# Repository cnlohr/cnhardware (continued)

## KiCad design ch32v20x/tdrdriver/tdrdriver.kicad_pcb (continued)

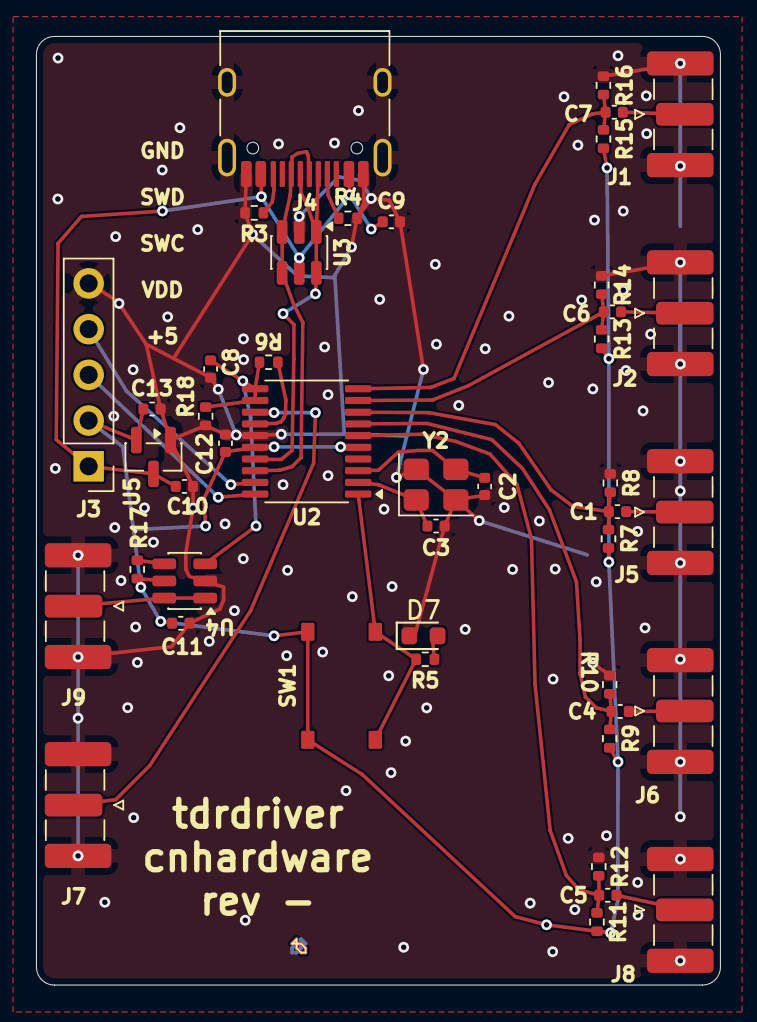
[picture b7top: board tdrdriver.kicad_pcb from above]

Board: 2 copper layers, 38.0 x 52.7 mm, 45 parts (0 on the bottom side), 28 nets.

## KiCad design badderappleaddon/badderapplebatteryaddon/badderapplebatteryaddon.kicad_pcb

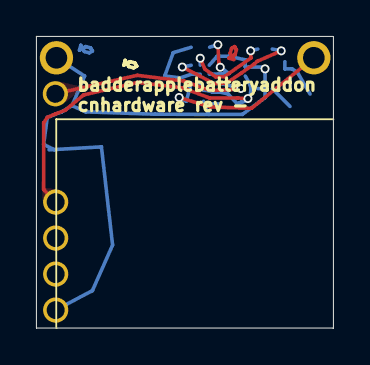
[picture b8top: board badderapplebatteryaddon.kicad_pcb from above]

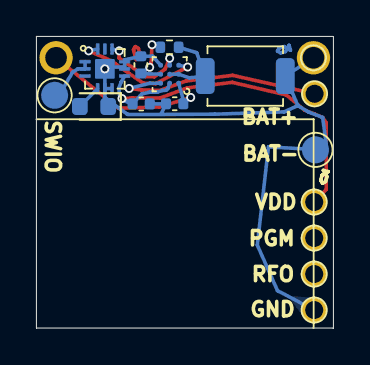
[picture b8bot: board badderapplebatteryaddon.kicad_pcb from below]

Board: 2 copper layers, 16.5 x 16.2 mm, 17 parts (16 on the bottom side), 10 nets.

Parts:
C1, C2: 100n; C_0402_1005Metric
C3: 1u; C_0402_1005Metric
D1: LED; LED_0603_1608Metric
J3: PGM; TestPoint_Pad_D1.0mm
J4: VDD; TestPoint_Pad_D1.0mm
J5, J11: GND; TestPoint_Pad_D1.0mm
J6: RFO; TestPoint_Pad_D1.0mm
J7: BAT+; TestPoint_Pad_D1.0mm
J10: VBUS
J82: SWIO; TestPoint_Pad_D1.5mm
R6: 5.1k; R_0402_1005Metric
SW1: TS; SW_SPST_TS-1088-xR020
TP13: BAT-; TestPoint_Pad_D1.5mm
U1: WLCSP-9-P0.5mm
U2: CH32V005D6U6; QFN-12-P0.4-WCH

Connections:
GND: C1.2, C2.2, C3.2, D1.1 (K), J5.1 (1_1), J11.1 (1_1), SW1.3 (B), TP13.1 (1_1), U1.C3 (GND), U2.2 (PA2/T1C2N/OPP0/XO/A0), U2.3 (PD0/T1C1N/SDA_/TX_/OPN1), U2.5 (PC0/T1C3_/T2C3), U2.6 (PC3/T1C3/T1C1N_), U2.13 (PAD)
LED: D1.2 (A), U2.1 (PA1/T1C2/OPN0/XI/A1)
unnamed: J82.1 (1_1), U2.10 (PD1/SWIO/T1C3N/SCL_/RX_), U2.11 (PD4/T1C4_/T2C1/OPO/A7)
PWRINT: R6.1, SW1.1 (A), U1.B1 (NTC), U1.B2 (INT)
SCL: U1.C2 (SCL), U2.7 (PC4/T1C4/T1C1_/T1C2N/MCO/A2)
SDA: U1.C1 (SDA), U2.9 (PC7/T1C2_/T2C2_)
VBAT: J7.1 (1_1), U1.A3 (BAT)
VBUS: C2.1, J10.1 (1_1), U1.A1 (IN)
VDD: C1.1, J4.1 (1_1), U1.A2 (SYS), U2.4 (VDD)
VSYS: C3.1, R6.2, U1.B3 (VDD)

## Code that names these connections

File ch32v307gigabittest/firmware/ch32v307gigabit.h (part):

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#endif

#ifndef CH32V307GIGABIT_PHY_RSTB
#define CH32V307GIGABIT_PHY_RSTB PA10
#endif


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	funDigitalWrite( CH32V307GIGABIT_PHY_RSTB, FUN_LOW );

	// Configure strapping.
	funPinMode( PA1, GPIO_CFGLR_IN_PUPD ); // GMII_RXD3
	funPinMode( PA0, GPIO_CFGLR_IN_PUPD ); // GMII_RXD2
	funPinMode( PC3, GPIO_CFGLR_IN_PUPD ); // GMII_RXD1
	funPinMode( PC2, GPIO_CFGLR_IN_PUPD ); // GMII_RXD0
	funDigitalWrite( PA1, FUN_HIGH );
	funDigitalWrite( PA0, FUN_HIGH );
	funDigitalWrite( PC3, FUN_HIGH ); // No TX Delay
	funDigitalWrite( PC2, FUN_HIGH );

	// Pull-up MDIO
	funPinMode( PD9, GPIO_CFGLR_OUT_50Mhz_PP ); //Pull-up control (DO NOT CHECK IN, ADD RESISTOR)
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
	// Switch to PLL.
#ifdef CH32V307GIGABIT_MCO25
	RCC->CFGR0 = (RCC->CFGR0 & ~RCC_SW) | RCC_SW_PLL | (9<<24); // And output clock on PA8
#else
	RCC->CFGR0 = (RCC->CFGR0 & ~RCC_SW) | RCC_SW_PLL;
#endif

	// For clock in.
	funPinMode( PB1, GPIO_CFGLR_IN_FLOAT ); //GMII_CLK125

	RCC->CFGR2 |= RCC_ETH1G_125M_EN; // Enable 125MHz clock.

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	// Use RGMII
	EXTEN->EXTEN_CTR |= EXTEN_ETH_RGMII_SEL; //EXTEN_ETH_RGMII_SEL;

	funPinMode( PB13, GPIO_CFGLR_OUT_50Mhz_AF_PP ); //GMII_MDIO
	funPinMode( PB12, GPIO_CFGLR_OUT_50Mhz_AF_PP ); //GMII_MDC

	// For clock output to Ethernet module.
	funPinMode( PA8, GPIO_CFGLR_OUT_50Mhz_AF_PP ); // PHY_CKTAL

	// Release PHY from reset.
	funDigitalWrite( CH32V307GIGABIT_PHY_RSTB, FUN_HIGH );

	funPinMode( PB0, GPIO_CFGLR_OUT_50Mhz_AF_PP ); // GMII_TXD3
	funPinMode( PC5, GPIO_CFGLR_OUT_50Mhz_AF_PP ); // GMII_TXD2
	funPinMode( PC4, GPIO_CFGLR_OUT_50Mhz_AF_PP ); // GMII_TXD1
	funPinMode( PA7, GPIO_CFGLR_OUT_50Mhz_AF_PP ); // GMII_TXD0
	funPinMode( PA3, GPIO_CFGLR_OUT_50Mhz_AF_PP ); // GMII_TXCTL
	funPinMode( PA2, GPIO_CFGLR_OUT_50Mhz_AF_PP ); // GMII_TXC
	funPinMode( PA1, GPIO_CFGLR_IN_PUPD ); // GMII_RXD3
	funPinMode( PA0, GPIO_CFGLR_IN_PUPD ); // GMII_RXD2
	funPinMode( PC3, GPIO_CFGLR_IN_PUPD ); // GMII_RXD1
	funPinMode( PC2, GPIO_CFGLR_IN_PUPD ); // GMII_RXD0
	funPinMode( PC1, GPIO_CFGLR_IN_PUPD ); // GMII_RXCTL
	funPinMode( PC0, GPIO_CFGLR_IN_FLOAT ); // GMII_RXC

	funDigitalWrite( PA1, FUN_HIGH ); // SELGRV = 3.3V
	funDigitalWrite( PA0, FUN_HIGH ); // TXDelay = 1
	funDigitalWrite( PC3, FUN_HIGH ); // AN[0] = 1
	funDigitalWrite( PC2, FUN_HIGH ); // AN[1] = 1
	funDigitalWrite( PC1, FUN_LOW );  // PHYAD[0]

	// Power on and reset.
	RCC->AHBPCENR |= RCC_ETHMACEN | RCC_ETHMACTXEN | RCC_ETHMACRXEN;
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
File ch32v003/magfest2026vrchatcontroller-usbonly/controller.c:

#include "ch32fun.h"
#include <stdio.h>
#include <string.h>
#include "rv003usb.h"

uint32_t clickcount = 0;
uint32_t clickcount_raw = 0;
uint32_t activate_time = 0;
int is_activated = 0;

//6 seconds
#define BONUS_TIME 240000000
#define MAX_CLICKS 420

typedef struct {
	volatile uint8_t len;
	uint8_t buffer[8];
} midi_message_t;

midi_message_t midi_in;

// midi data from device -> host (IN)
void midi_send(uint8_t * msg, uint8_t len)
{
	memcpy( midi_in.buffer, msg, len );
	midi_in.len = len;
}
#define midi_send_ready() (midi_in.len == 0)

// Set up PC2 to PC5 as inputs
void keyboard_init( void )
{
	// Enable GPIOC
	RCC->APB2PCENR |= RCC_APB2Periph_GPIOC | RCC_APB2Periph_GPIOD | RCC_APB2Periph_GPIOA | RCC->APB2PCENR | RCC_APB2Periph_USART1 | RCC_APB2Periph_AFIO;

	funDigitalWrite( PA1, 1 );
	funDigitalWrite( PA2, 1 );
	funDigitalWrite( PD2, 1 );
	funDigitalWrite( PD6, 1 );
	funDigitalWrite( PD7, 1 );
	funDigitalWrite( PC0, 1 );
	funDigitalWrite( PC1, 1 );
	funDigitalWrite( PC2, 1 );
	funDigitalWrite( PC3, 1 );
	funDigitalWrite( PC4, 1 );
	funDigitalWrite( PC5, 1 );
	funDigitalWrite( PC6, 1 );
	funDigitalWrite( PC7, 1 );

	funPinMode( PA1, GPIO_CFGLR_IN_PUPD );
	funPinMode( PA2, GPIO_CFGLR_IN_PUPD );
	funPinMode( PD2, GPIO_CFGLR_IN_PUPD );
	funPinMode( PD6, GPIO_CFGLR_IN_PUPD );
	funPinMode( PD7, GPIO_CFGLR_IN_PUPD );
	funPinMode( PC0, GPIO_CFGLR_IN_PUPD );
	funPinMode( PC1, GPIO_CFGLR_IN_PUPD );
	funPinMode( PC2, GPIO_CFGLR_IN_PUPD );
	funPinMode( PC3, GPIO_CFGLR_IN_PUPD );
	funPinMode( PC4, GPIO_CFGLR_IN_PUPD );
	funPinMode( PC5, GPIO_CFGLR_IN_PUPD );
	funPinMode( PC6, GPIO_CFGLR_IN_PUPD );
	funPinMode( PC7, GPIO_CFGLR_IN_PUPD );


	// Set UART baud rate here
	#define UART_BR 115200

	// Push-Pull, 10MHz Output on D0, with AutoFunction, USART1_RM=01
	funPinMode( PD0, GPIO_CFGLR_OUT_10Mhz_AF_PP );

	AFIO->PCFR1 = AFIO_PCFR1_USART1_REMAP;

	// Setup UART for Tx 8n1
	USART1->CTLR1 = USART_WordLength_8b | USART_Parity_No | USART_Mode_Tx;
	USART1->CTLR2 = USART_StopBits_2;

	// Set baud rate and enable UART
	USART1->BRR = ((FUNCONF_SYSTEM_CORE_CLOCK) + (UART_BR)/2) / (UART_BR);
	USART1->CTLR1 |= CTLR1_UE_Set;
}

void scan_keyboard(void)
{
	uint32_t input = GPIOC->INDR | ( GPIOD->INDR << 8 ) | ( GPIOA->INDR<<16);
	static uint32_t last_input;
	static uint32_t last_down[24];
	input &= 0b1101100010011111111;
	
	int dcc = 0;
	int i;
	uint32_t mask = input ^ last_input;
	mask &= ~input;
	uint32_t now = SysTick->CNT;
	static uint32_t pending = 0;

	// Debounce down press only.
	for( i = 0; i < 24; i++ )
	{
		if( (mask & (1<<i)) )
		{
			last_down[i] = now;
			pending |= (1<<i);
		}
		if( (now - last_down[i]) > 960000 ) //20ms debounce
		{
			if( (pending&(1<<i)) )
			{
				if( ( input & (1<<i)) == 0 ) 
					dcc++;
			}
			pending&=~(1<<i);
		}

	}
	clickcount+=dcc;
	clickcount_raw+=dcc;

	if( clickcount >= MAX_CLICKS && !is_activated )
	{
		clickcount = MAX_CLICKS;
		is_activated = 1;
		activate_time = SysTick->CNT;
	}

	if( is_activated && ( (SysTick->CNT - activate_time) > BONUS_TIME ) )
	{
		is_activated = 0;
		activate_time = 0;
		clickcount = 0;
	}

	if( midi_send_ready() )
	{
		uint8_t midi_msg[4] = {0x09, 0xB0, 0x40, 0x7F}; // Control Channel
		midi_msg[2] = (clickcount >> 3);
		midi_msg[3] = (clickcount & 7)<<4;
//printf( "%d\n", clickcount );
		midi_send(midi_msg, 4);
	}

	last_input = input;
}

int main()
{
	SystemInit();
	keyboard_init();
	usb_setup();
	int fct = 0;
	while(1)
	{
		scan_keyboard();

		if((fct & 0x7)== 0)
		{
			USART1->DATAR = (clickcount_raw & 0x3f) | ( is_activated ? 0x80 : 0x00);
			//printf( "!\n" );
		}
		Delay_Us(200);
		fct++;
	}
}

void usb_handle_user_in_request( struct usb_endpoint * e, uint8_t * scratchpad, int endp, uint32_t sendtok, struct rv003usb_internal * ist )
{
	if (endp && midi_in.len) {
		usb_send_data( midi_in.buffer, midi_in.len, 0, sendtok );
		midi_in.len = 0;
	} else {
		usb_send_empty( sendtok );
	}
}

void usb_handle_other_control_message( struct usb_endpoint * e, struct usb_urb * s, struct rv003usb_internal * ist )
{
	LogUEvent( SysTick->CNT, s->wRequestTypeLSBRequestMSB, s->lValueLSBIndexMSB, s->wLength );
}

void usb_handle_user_data( struct usb_endpoint * e, int current_endpoint, uint8_t * data, int len, struct rv003usb_internal * ist )
{
//	if (len); //midi_receive(data);
//	if (len==8); //midi_receive(&data[4]);
}






/*

using UdonSharp;
using UnityEngine;
using VRC.SDKBase;
using VRC.Udon;

using TMPro;
public class MidiReceiver : UdonSharpBehaviour
{
	public TMP_Text tmp;
	public int frameno;
	
	public int lastVelocity;
	public int lastNoteNo;
	public int lastPercent420;
	
    void Start()
    {
        Debug.Log( "test" );
    }
	
	override public void MidiControlChange(int channel, int number, int velocity)
	{
		Debug.Log( $"MidiControlChange {channel} {number} {velocity}" );
		lastVelocity = velocity;
		lastNoteNo = number;
		lastPercent420 = number * 8 + velocity/16;
	}
	
	override public void MidiNoteOn(int channel, int number, int velocity)
	{
		Debug.Log( $"MidiNoteOn {channel} {number} {velocity}" );
		lastVelocity = velocity;
		lastNoteNo = number;
		lastPercent420 = number * 8 + velocity/16;
	}
	
	
	void Update()
	{
		frameno++;
		tmp.text = $"N:{frameno}\n{lastPercent420}";
	}
}
*/

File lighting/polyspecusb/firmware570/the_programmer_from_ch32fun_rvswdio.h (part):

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
#define CH5xx_SUPPORT 1

//#define POWER_IO    PA7
//#define SWC_IO      PA3
//#define SWD_IO      PA2

#define BB_PRINTF_DEBUG(x...) // printf( x )
#define IRAM_ATTR __HIGH_CODE
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						iptr += 6; // reserved + SDM values.
						(void)use_apll;
						(void)sdm0;
						// Output MCO clock on PC4.
						// Not implemented on 570
					}
					break;
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
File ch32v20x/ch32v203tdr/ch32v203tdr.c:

/* Small example showing how to use the SWIO programming pin to 
   do printf through the debug interface */

#include "ch32fun.h"
#include <stdio.h>

uint32_t count;

int main()
{
	SystemInit();

	// Force HSE.
	

	RCC->APB2PCENR |= RCC_APB2Periph_GPIOD | RCC_APB2Periph_GPIOC | RCC_APB2Periph_GPIOA | RCC_APB2Periph_TIM1 | RCC_APB2Periph_ADC1;

	RCC->CFGR0 |= RCC_ADCPRE_DIV8; // Divide ADC timer
	RCC->CTLR &= ~3; // HSI Off

	// Configure ADC first.
	// Note to self: DO NOT USE BUFFER
	ADC1->CTLR1 = ( 0 << 0);
	ADC1->CTLR2 = ADC_EXTTRIG | ADC_ADON | ( 0 << 17 ); // EXTSEL = T1CC1
	ADC1->SAMPTR2 = 0; // 1.5 cycle SAMPTR = 0, 1 = 7.5 samples, does not change edge

	// Prescaler (Actually run TIM1 @ 144MHz)
	TIM1->PSC = 0x0000;


	// Actual time is this+1
	// Must be divisible by ADC setup.
	TIM1->ATRLR = 511;

	TIM1->SWEVGR |= TIM_UG;
	
	TIM1->CCER |= TIM_CC1E | TIM_CC1P;
	TIM1->CCER |= TIM_CC4E | TIM_CC4P;
	TIM1->CHCTLR1 |= TIM_OC1M_2 | TIM_OC1M_1;
	TIM1->CHCTLR2 |= TIM_OC4M_2 | TIM_OC4M_1;

	TIM1->CH1CVR = 68; // CH1 triggers ADC.  Be careful where this is set.
	TIM1->CH4CVR = 4; // This is what we are controlling.

	TIM1->CTLR1 = 0;

	// Enable TIM1 outputs
	TIM1->BDTR |= TIM_MOE;
	TIM1->CTLR1 |= TIM_CEN;

	funPinMode( PA0, GPIO_CNF_IN_ANALOG );

	// PWM outputs.  We only actually use PA11, PA8 is diagnostic for the ADC trigger.
	funPinMode( PA8, GPIO_Speed_50MHz | GPIO_CNF_OUT_PP_AF );
	funPinMode( PA9, GPIO_Speed_50MHz | GPIO_CNF_OUT_PP_AF );
	funPinMode( PA10, GPIO_Speed_50MHz | GPIO_CNF_OUT_PP_AF );
	funPinMode( PA11, GPIO_Speed_50MHz | GPIO_CNF_OUT_PP_AF );

	int framestart = 60;
	int frame = framestart;
	int32_t vals[128];

	while(1)
	{
		memset( vals, 0, sizeof( vals ) );
		int i;
		(void)ADC1->RDATAR;
		for( i = 30; i < 92; i++ )
		{
			int j;
			for( j = 0; j < 16; j++ )
			{
				while(!(ADC1->STATR & ADC_EOC));
				vals[i] += ADC1->RDATAR;
				TIM1->CH4CVR = i;
			}
		}
		for( i = 30; i < 92; i++ )
		{
			printf( "%d ", (int)vals[i] );
		}
		printf( "\n" );
	}
}

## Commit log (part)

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2025-06-28 Tweak parts
2025-07-08 Undo Update README.md
2025-07-08 Add stuff for inductance tracking
2025-07-09 Update some new parts
2025-07-09 Add datasheet
2025-07-11 Add some missing hardware
2025-07-12 Add ch570 saob test
2025-07-12 Update PCB
2025-07-12 Bump design
2025-07-12 Add keytar touch
2025-07-12 Update kboards for ordering
2025-07-12 Update with kicad stuff
2025-07-12 Update design
2025-07-13 Bump versions
2025-07-13 Bump
2025-07-18 Bump keytar files
2025-07-19 Bump itty bitty
2025-07-19 Bump kicad parts
2025-07-20 Bump ittyahrs
2025-07-20 Tweak tinyahrs
2025-07-20 Tweaking board
2025-07-21 Bump hexi test
2025-07-22 Playing with other structures
2025-07-22 Poking around
2025-07-26 Add test firmware
2025-07-26 Update with notes to do.
2025-07-26 Basic firmware test
2025-07-26 Add ch570 port of the sao game.
2025-07-26 Bump sao game
2025-07-26 Update firmwares
2025-07-27 bump config
2025-07-27 Bump designs
2025-07-27 Add some basic test stuff. No QMI yet.
2025-07-28 Working firmware examples
2025-07-28 Bump design overall
2025-07-28 Add some neat adc stuff
2025-07-28 Bump code test
2025-07-29 Bump ch570 design
2025-07-30 Bump technique using sleep
2025-07-30 Add timer based mechanism for ADC
2025-07-30 bump exploration
2025-07-30 make main loop control release, etc.
2025-07-30 Add buck
2025-08-05 Update design with new ch570 board
2025-08-05 Update designs
2025-08-05 Poke design
2025-08-05 Bump submodule
2025-08-06 Bump all designs per order
2025-08-07 Working on design
2025-08-08 Bump design by order
2025-08-08 Bump all designs for order
2025-08-08 Bump designs per purchase
2025-08-08 Bump based on actual board order
2025-08-17 resaved scheamtci
2025-08-19 Add notes about repo moving
2025-08-22 Add some parts
2025-08-22 Bump aa only swadge
2025-08-22 Tweak design
2025-08-24 Bump library
2025-08-24 Bump aa swadge
2025-08-24 Bump with new wsled changes
2025-08-24 Update with revA for 006 board
2025-08-29 Bump with thinking about ch570 swadge
2025-08-31 List some up/down converters
2025-09-01 Bump readme
2025-09-03 Update with addlepated array
2025-09-04 Update parts
2025-09-07 Bump disign!
2025-09-08 Bump amp
2025-09-08 Update notes on amp
2025-09-10 Tweak designs
2025-09-10 Forgot to commit component
2025-09-28 Bump gigabit test
2025-09-30 update rev as it's in the other repo but leave it here
2025-10-03 Cleanup making the usb connector have paste
2025-10-03 Thicken power traces, use a SOT-23 regulator
2025-10-28 9v battery sao test
2025-10-29 Bump with battery model
2025-11-04 Bump scope
2025-11-05 Update scope
2025-11-05 revert upping design
2025-11-10 Bump 9v sao
2025-11-10 Fix based on comments from fab
2025-11-10 add ch32v208 part
2025-11-10 Update to actual pritn
2025-11-16 fix version
2025-11-16 Udpate design
2025-11-16 Update with opa564
2025-11-18 Revert version
2025-11-18 Add notes in todo
2025-11-18 Update with basic idea
2025-11-19 Bump lib
2025-11-20 Bump design per order
2025-11-25 Working firmware in i2c and spi
2025-11-25 Add basic test example with adc
2025-11-25 Change name
2025-11-25 ADd notes
2025-11-25 Update with timing note
2025-11-25 cleanup
2025-11-25 Update notes
2025-11-26 Update tiatest with functional rev
2025-11-26 Update part
2025-11-26 Add testing code
2025-11-27 Working with vsync ~170Hz
2025-11-30 Add a sleep mode
2025-11-30 Add some code for a raw smps test
2025-12-01 examining a pfs programmer
2025-12-03 Update with notes about charge pumps
2025-12-03 Per order
2025-12-05 Update with a basic emulator
2025-12-05 update emu getting closer
2025-12-06 Update firmware to allow for emulated pressure
2025-12-08 Fixup firmware for using full dual sets.
2025-12-08 Fixup timings for 3 strips simultaneously
2025-12-08 Move project
2025-12-08 Add move note
2025-12-11 Update with some work on my current monitor
2025-12-11 Fixup design a little
2025-12-11 Update symbols
2025-12-12 Update all parts from tonight
2025-12-12 Add order files
2025-12-12 Bump to what was actually ordered
2025-12-12 Switch to better opamp
2025-12-12 Add note
2025-12-13 Update with new parts
2025-12-24 Update and add controller example
2026-01-06 Tweaks from windows side
2026-01-06 Update with working tubes and stuff
2026-01-06 Update for real build
2026-01-06 Oops forgot one more tweak
2026-01-07 Tweak total boss active time
2026-01-08 Add counter+ Change speed
2026-01-09 CH32V003 SAO firmware
2026-01-09 Update firmware to build
2026-01-09 Add note about maybe wrong
2026-01-12 Add demoswadge discussion
2026-01-12 Add rest of specs
2026-01-12 Further tweak with LSM6DS3
2026-01-12 Further tweaks
2026-01-12 Fix table note
2026-01-12 Fix cost spacing
2026-01-12 More tweaks
2026-01-12 Update proposal
2026-01-12 Bump further
2026-01-12 Tweak further
2026-01-12 More notes
2026-01-12 Add ch584
2026-01-12 tweak design for CH584
2026-01-12 Update kicad parts and swadge notes
2026-01-12 Update with some swadge stuff
2026-01-12 Add note about internal RTC.
2026-01-13 Bump demoswadge
2026-01-14 Update submodules Update demo swadge Update kicad parts Update new frogswadge
2026-01-14 Forgot to add extra file
2026-01-15 Update with a new style swadge
2026-01-15 Bump froggy
2026-01-19 Bump add buck
2026-01-19 update froggy/test
2026-01-19 Add selected fpc
2026-02-01 Add dmc
2026-02-01 Bump funprog
2026-02-03 Bump desing for 570+584
2026-02-05 add parts
2026-02-09 Bump to rev A
2026-02-09 Bump rev
2026-02-09 Add canitcam for 006
2026-02-10 Add note about tamagotchi
2026-02-12 Bump tadpole swadge
2026-02-12 Update boards
2026-02-16 Add layer 3
2026-02-16 Add RF Playground
2026-02-17 Update from send to friends
2026-03-16 trying to get pwm working
2026-05-01 Add example
2026-05-01 Float middle pin
2026-05-02 playing aroundo
2026-05-03 Working on usbpdtest
2026-05-03 Prorgess
2026-05-04 Playing more with CRCs
2026-05-04 Add link note
2026-05-06 Table based almost working
2026-05-10 Update PD codeo
2026-05-10 Testing continues
2026-05-11 Code cleanup
2026-05-14 ADd demoboard
2026-05-14 Add demoboard for pfc
2026-05-16 Update hpyerspec
2026-05-16 Move over some files
2026-05-16 fix: V-001 security vulnerability
    Automated security fix generated by Orbis Security AI
2026-05-28 Bump inductance measurement
2026-05-31 Poking at ch570 work
2026-05-31 Pking at the problem more
2026-06-03 Update files
2026-06-03 Glitch no workie
2026-06-04 Bump design workAnd properly name polypsec
2026-06-04 Update polyspec
2026-06-04 Add notes for LEDs to test
2026-06-13 Add missing parts
2026-06-16 Update testing
2026-06-17 Progress
2026-06-18 Add funboard
2026-06-18 Tweak pinout
2026-06-18 Bump board
2026-06-24 Update board
2026-06-24 Bump notes
2026-06-24 Bump and rename
2026-06-24 bump 208 board
2026-06-24 Bump with rev -
